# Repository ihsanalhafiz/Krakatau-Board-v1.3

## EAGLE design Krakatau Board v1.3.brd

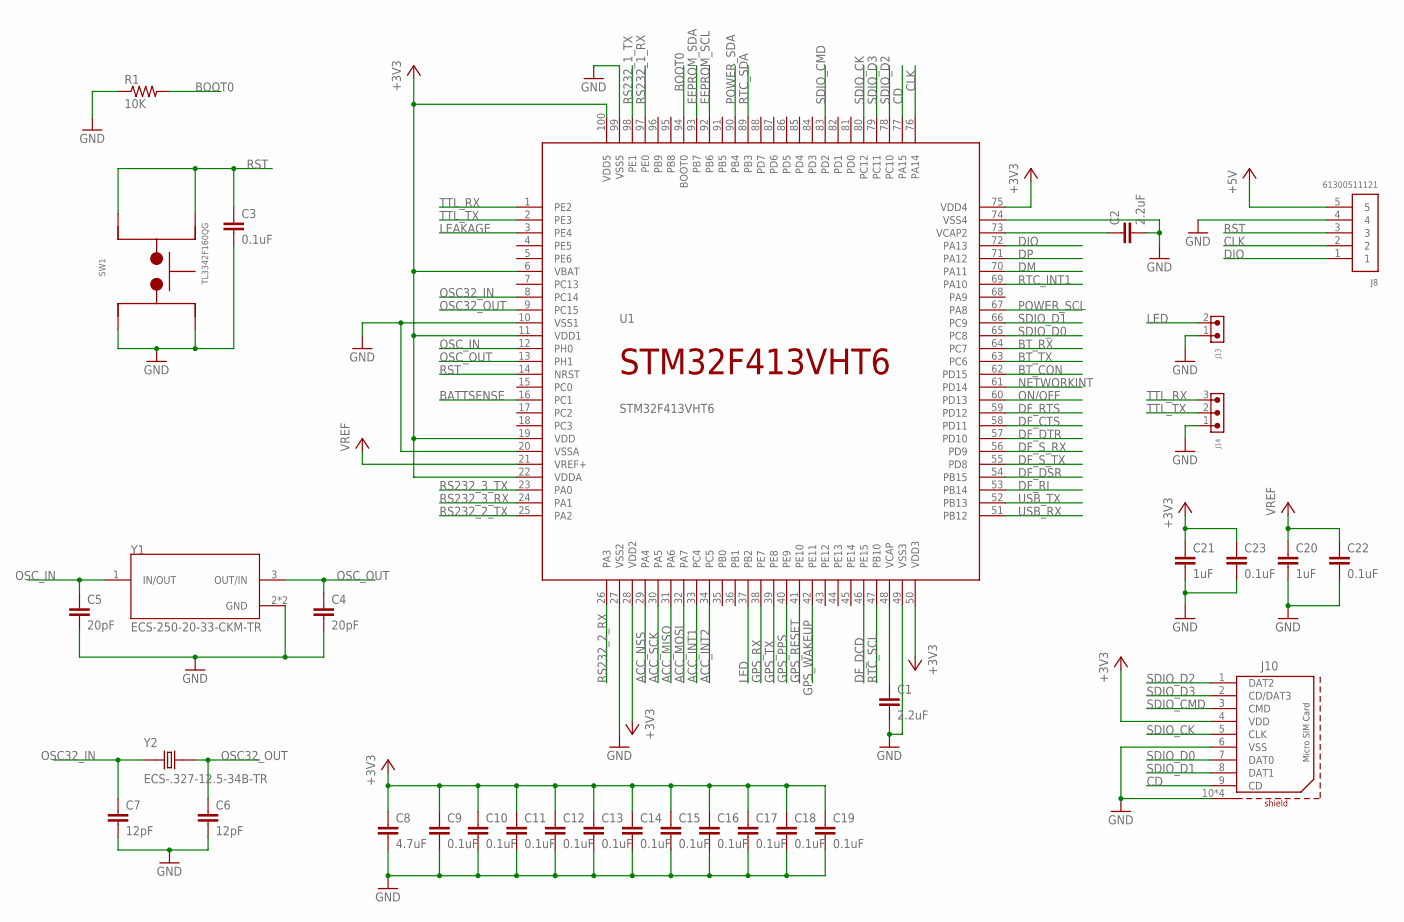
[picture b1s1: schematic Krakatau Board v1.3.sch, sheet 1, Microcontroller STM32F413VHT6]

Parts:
C1, C2: 2.2uF; CAPC1005X50N-0402-KEMET
C3, C9, C10, C11, C12, C13, C14, C15, C16, C17, C18, C19, C22, C23: 0.1uF; CAPC1005X50N-0402-KEMET
C4, C5: 20pF; CAPC1005X50N-0402-KEMET
C6, C7: 12pF; CAPC1005X50N-0402-KEMET
C8: 4.7uF; CAPC3225X90N-1210-KEMET
C20, C21: 1uF; CAPC1608X80N-0603-KEMET
J8: 61300511121
J10: 693071020811
J13: 61900211121
J14: 61900311121
R1: 10K; RESC1005X35N-0402-VISHAYDALE
SW1: TL3342F160QG; SW_TL3342F160QG
U1: STM32F413VHT6; QFP50P1590X1590X160-100N
Y1: ECS-250-20-33-CKM-TR; XTAL_ECS-250-20-33-CKM-TR
Y2: ECS-.327-12.5-34B-TR; XTAL_ECS-.327-12.5-34B-TR

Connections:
+3V3: C8.1, C9.1, C10.1, C11.1, C12.1, C13.1, C14.1, C15.1, C16.1, C17.1, C18.1, C19.1, C21.1, C23.1, J10.4 (VDD), U1.6 (VBAT), U1.11 (VDD1), U1.19 (VDD), U1.22 (VDDA), U1.28 (VDD2), U1.50 (VDD3), U1.75 (VDD4), U1.100 (VDD5); also elsewhere on the board
+5V: J8.5; also elsewhere on the board
ACC_INT1: U1.33 (PC4); also elsewhere on the board
ACC_INT2: U1.34 (PC5); also elsewhere on the board
ACC_MISO: U1.31 (PA6); also elsewhere on the board
ACC_MOSI: U1.32 (PA7); also elsewhere on the board
ACC_NSS: U1.29 (PA4); also elsewhere on the board
ACC_SCK: U1.30 (PA5); also elsewhere on the board
BATTSENSE: U1.16 (PC1); also elsewhere on the board
BOOT0: R1.2, U1.94 (BOOT0)
BT_CON: U1.62 (PD15); also elsewhere on the board
BT_RX: U1.64 (PC7); also elsewhere on the board
BT_TX: U1.63 (PC6); also elsewhere on the board
CD: J10.9 (CD), U1.77 (PA15)
CLK: J8.2, U1.76 (PA14)
DF_CTS: U1.58 (PD11); also elsewhere on the board
DF_DCD: U1.46 (PE15); also elsewhere on the board
DF_DSR: U1.54 (PB15); also elsewhere on the board
DF_DTR: U1.57 (PD10); also elsewhere on the board
DF_RI: U1.53 (PB14); also elsewhere on the board
DF_RTS: U1.59 (PD12); also elsewhere on the board
DF_S_RX: U1.56 (PD9); also elsewhere on the board
DF_S_TX: U1.55 (PD8); also elsewhere on the board
DIO: J8.1, U1.72 (PA13)
DM: U1.70 (PA11)
DP: U1.71 (PA12)
EEPROM_SCL: U1.92 (PB6); also elsewhere on the board
EEPROM_SDA: U1.93 (PB7); also elsewhere on the board
GND: C1.2, C2.2, C3.2, C4.2, C5.2, C6.2, C7.2, C8.2, C9.2, C10.2, C11.2, C12.2, C13.2, C14.2, C15.2, C16.2, C17.2, C18.2, C19.2, C20.2, C21.2, C22.2, C23.2, J8.4, J10.6 (VSS), J10.10 (SHIELD), J10.11 (SHIELD), J10.12 (SHIELD), J10.13 (SHIELD), J13.1, J14.1, R1.1, SW1.1, SW1.2, U1.10 (VSS1), U1.20 (VSSA), U1.27 (VSS2), U1.49 (VSS3), U1.74 (VSS4), U1.99 (VSS5), Y1.2 (GND), Y1.4 (GND); also elsewhere on the board
GPS_PPS: U1.40 (PE9); also elsewhere on the board
GPS_RESET: U1.41 (PE10); also elsewhere on the board
GPS_RX: U1.38 (PE7); also elsewhere on the board
GPS_TX: U1.39 (PE8); also elsewhere on the board
GPS_WAKEUP: U1.42 (PE11); also elsewhere on the board
LEAKAGE: U1.3 (PE4); also elsewhere on the board
LED: J13.2, U1.37 (PB2)
unnamed: C2.1, U1.73 (VCAP2)
unnamed: C1.1, U1.48 (VCAP)
NETWORKINT: U1.61 (PD14); also elsewhere on the board
ON/OFF: U1.60 (PD13); also elsewhere on the board
OSC32_IN: C7.1, U1.8 (PC14), Y2.1
OSC32_OUT: C6.1, U1.9 (PC15), Y2.2
OSC_IN: C5.1, U1.12 (PH0), Y1.1 (IN/OUT)
OSC_OUT: C4.1, U1.13 (PH1), Y1.3 (OUT/IN)
POWER_SCL: U1.67 (PA8); also elsewhere on the board
POWER_SDA: U1.90 (PB4); also elsewhere on the board
RS232_1_RX: U1.97 (PE0); also elsewhere on the board
RS232_1_TX: U1.98 (PE1); also elsewhere on the board
RS232_2_RX: U1.26 (PA3); also elsewhere on the board
RS232_2_TX: U1.25 (PA2); also elsewhere on the board
RS232_3_RX: U1.24 (PA1); also elsewhere on the board
RS232_3_TX: U1.23 (PA0); also elsewhere on the board
RST: C3.1, J8.3, SW1.3, SW1.4, U1.14 (NRST)
RTC_INT1: U1.69 (PA10); also elsewhere on the board
RTC_SCL: U1.47 (PB10); also elsewhere on the board
RTC_SDA: U1.89 (PB3); also elsewhere on the board
SDIO_CK: J10.5 (CLK), U1.80 (PC12)
SDIO_CMD: J10.3 (CMD), U1.83 (PD2)
SDIO_D0: J10.7 (DAT0), U1.65 (PC8)
SDIO_D1: J10.8 (DAT1), U1.66 (PC9)
SDIO_D2: J10.1 (DAT2), U1.78 (PC10)
SDIO_D3: J10.2 (CD/DAT3), U1.79 (PC11)
TTL_RX: J14.3, U1.1 (PE2)
TTL_TX: J14.2, U1.2 (PE3)
USB_RX: U1.51 (PB12); also elsewhere on the board
USB_TX: U1.52 (PB13); also elsewhere on the board
VCC: C20.1, C22.1, U1.21 (VREF+); also elsewhere on the board

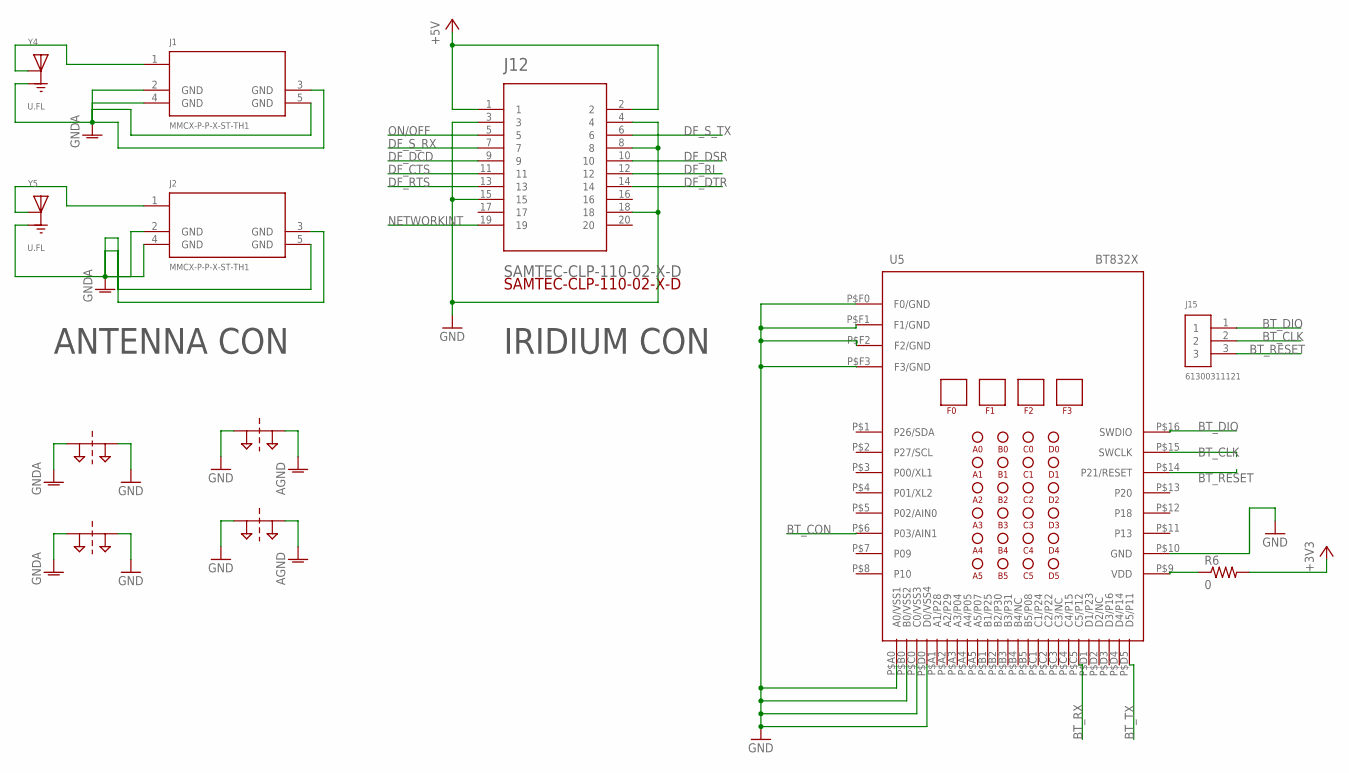
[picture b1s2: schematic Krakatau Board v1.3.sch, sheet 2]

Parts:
J1, J2: MMCX-P-P-X-ST-TH1
J12: SAMTEC-CLP-110-02-X-D
J15: 61300311121
R6: 0; RESC1005X30N
SUPPLY4, SUPPLY5, SUPPLY6, SUPPLY7: 2PT_GND_TIE
U5: BT832X
Y4, Y5: U.FL; HRS_U.FL-R-SMT-1(10)

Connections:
+3V3: R6.2; also elsewhere on the board
+5V: J12.1, J12.2; also elsewhere on the board
AGND: SUPPLY5.P$2, SUPPLY6.P$2; also elsewhere on the board
BT_CLK: J15.2, U5.P$15 (SWCLK)
BT_CON: U5.P$6 (P03/AIN1); also elsewhere on the board
BT_DIO: J15.1, U5.P$16 (SWDIO)
BT_RESET: J15.3, U5.P$14 (P21/RESET)
BT_RX: U5.P$C5 (C5/P12); also elsewhere on the board
BT_TX: U5.P$D5 (D5/P11); also elsewhere on the board
DF_CTS: J12.11; also elsewhere on the board
DF_DCD: J12.9; also elsewhere on the board
DF_DSR: J12.10; also elsewhere on the board
DF_DTR: J12.14; also elsewhere on the board
DF_RI: J12.12; also elsewhere on the board
DF_RTS: J12.13; also elsewhere on the board
DF_S_RX: J12.7; also elsewhere on the board
DF_S_TX: J12.6; also elsewhere on the board
GND: J12.3, J12.4, J12.8, J12.15, J12.18, SUPPLY4.P$2, SUPPLY5.P$1, SUPPLY6.P$1, SUPPLY7.P$2, U5.P$10 (GND), U5.P$A0 (A0/VSS1), U5.P$B0 (B0/VSS2), U5.P$C0 (C0/VSS3), U5.P$D0 (D0/VSS4), U5.P$F0 (F0/GND), U5.P$F1 (F1/GND), U5.P$F2 (F2/GND), U5.P$F3 (F3/GND); also elsewhere on the board
GNDA: J1.2 (GND), J1.3 (GND), J1.4 (GND), J1.5 (GND), J2.2 (GND), J2.3 (GND), J2.4 (GND), J2.5 (GND), SUPPLY4.P$1, SUPPLY7.P$1, Y4.1 (GND), Y4.3 (GND), Y5.1 (GND), Y5.3 (GND)
unnamed: R6.1, U5.P$9 (VDD)
unnamed: J1.1, Y4.2 (SIG)
unnamed: J2.1, Y5.2 (SIG)
NETWORKINT: J12.19; also elsewhere on the board
ON/OFF: J12.5; also elsewhere on the board

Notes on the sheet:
ANTENNA CON
IRIDIUM CON

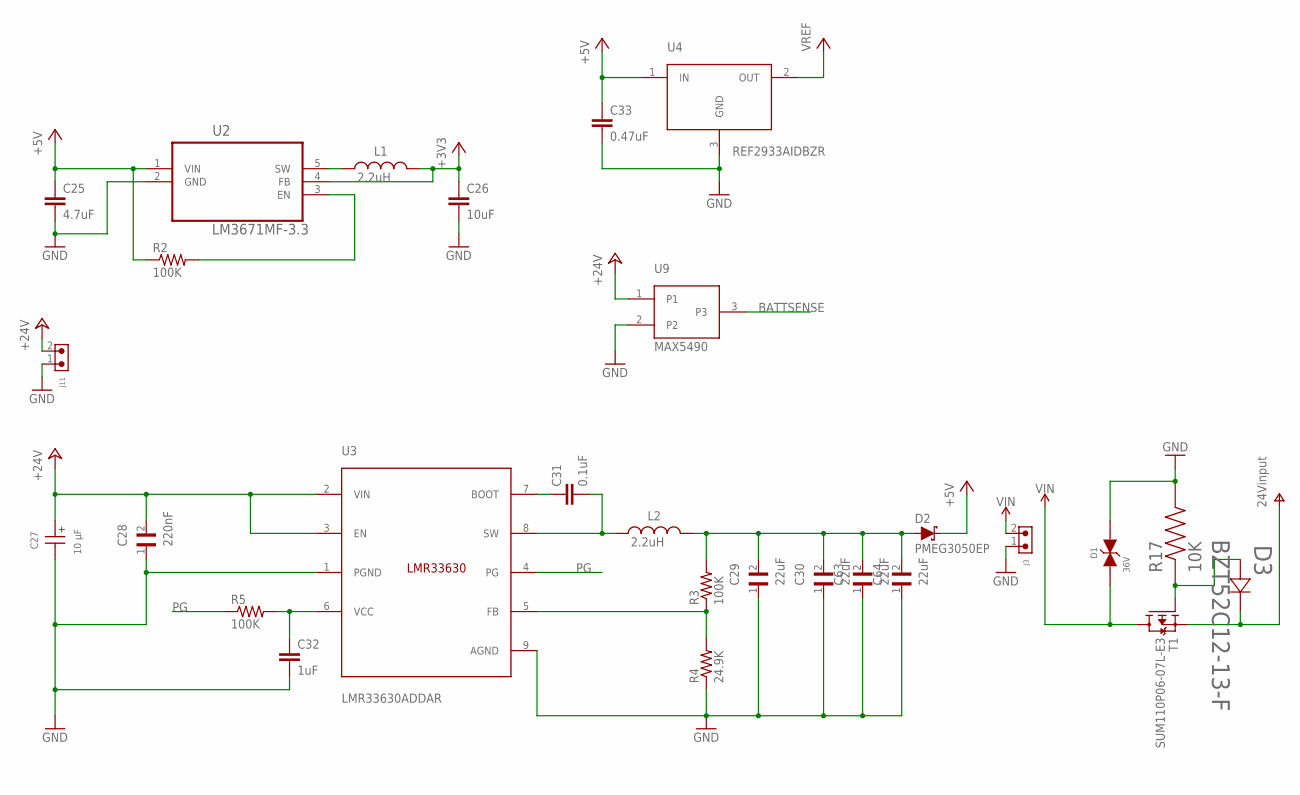
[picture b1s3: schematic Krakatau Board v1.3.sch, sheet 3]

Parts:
C25: 4.7uF; CAPC2113X90N-0805-KEMET
C26: 10uF; CAPC2113X90N-0805-KEMET
C27: 10 µF; WCAP-AS5H_5X5.5(DXL)
C28: 220nF; CAPC2012X100N
C29, C30, C63, C64: 22uF; CAPC2113X95N
C31: 0.1uF; CAPC1005X50N-0402-KEMET
C32: 1uF; CAPC1608X80N-0603-KEMET
C33: 0.47uF; CAPC1005X50N-0402-KEMET
D1: 36V; WE-TVSP_DO-214AB_BIDIRECTIONAL
D2: PMEG3050EP; SODFL4725X110N
D3: BZT52C12-13-F; SOD123_DIO
J3, J11: 61900211021
L1, L2: 2.2uH; WE-MAIA_4020
R2, R3, R5: 100K; RESC1005X35N-0402-VISHAYDALE
R4: 24.9K; RESC1005X30N
R17: 10K; RESC1608X55N
T1: SUM110P06-07L-E3; TO-263AB_SUM
U2: LM3671MF-3.3; SOT95P284X122-5N
U3: LMR33630ADDAR; SOIC127P600X170-9T260X310N
U4: REF2933AIDBZR; SOT95P237X112-3N
U9: MAX5490; SOT95P237X110-3

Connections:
+3V3: C26.1, L1.2, U2.4 (FB); also elsewhere on the board
+5V: C25.1, C33.1, D2.C, R2.1, U2.1 (VIN), U4.1 (IN); also elsewhere on the board
+24V: C27.1 (+), C28.2, J11.2, U3.2 (VIN), U3.3 (EN), U9.1; also elsewhere on the board
BATTSENSE: U9.3; also elsewhere on the board
GND: C25.2, C26.2, C27.2 (-), C28.1, C29.1, C30.1, C32.2, C33.2, C63.1, C64.1, D1.2, J3.1, J11.1, R4.1, R17.2, U2.2 (GND), U3.1 (PGND), U3.9 (AGND), U4.3 (GND), U9.2; also elsewhere on the board
unnamed: L1.1, U2.5 (SW)
unnamed: C31.1, U3.7 (BOOT)
unnamed: C29.2, C30.2, C63.2, C64.2, D2.A, L2.2, R3.2
unnamed: C32.1, R5.2, U3.6 (VCC)
unnamed: C31.2, L2.1, U3.8 (SW)
unnamed: R3.1, R4.2, U3.5 (FB)
unnamed: D3.2, R17.1, T1.1 (G)
unnamed: R2.2, U2.3 (EN)
PG: R5.1, U3.4 (PG)
V+: D3.1, T1.3 (S); also elsewhere on the board
VCC: U4.2 (OUT); also elsewhere on the board
VIN: D1.1, J3.2, T1.2 (D)

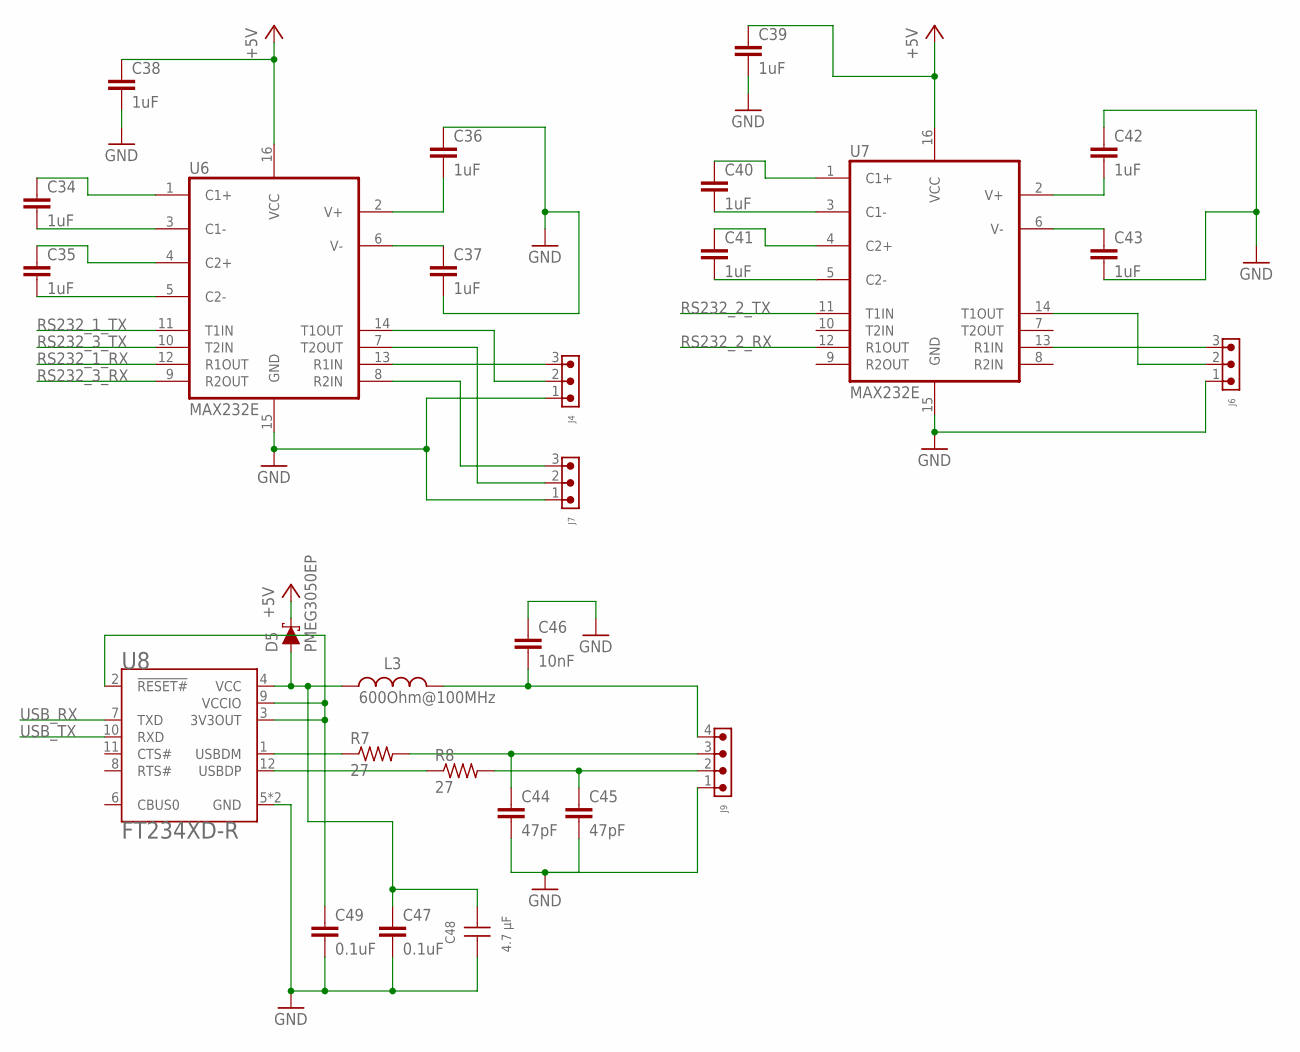
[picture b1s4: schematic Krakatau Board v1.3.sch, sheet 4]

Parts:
C34, C35, C36, C37, C38, C39, C40, C41, C42, C43: 1uF; CAPC1608X80N-0603-KEMET
C44, C45: 47pF; CAPC1005X50N-0402-KEMET
C46: 10nF; CAPC1005X50N-0402-KEMET
C47, C49: 0.1uF; CAPC1005X50N-0402-KEMET
C48: 4.7 µF; WCAP-CSGP_0402
D5: PMEG3050EP; SODFL4725X110N
J4, J6, J7: 61900311021
J9: 61900411121
L3: 600Ohm@100MHz; WE-CBF_0603(W=2.6)
R7, R8: 27; RESC1005X30N
U6, U7: MAX232E; SOIC127P1030X265-16N
U8: FT234XD-R; SON45P300X300X75-13N

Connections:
+5V: C38.1, C39.1, D5.C, U6.16 (VCC), U7.16 (VCC); also elsewhere on the board
GND: C36.1, C37.2, C38.2, C39.2, C42.1, C43.2, C44.2, C45.2, C46.1, C47.2, C48.1, C49.2, J4.1, J6.1, J7.1, J9.1, U6.15 (GND), U7.15 (GND), U8.5 (GND), U8.13 (GND); also elsewhere on the board
unnamed: J6.2, U7.14 (T1OUT)
unnamed: J6.3, U7.13 (R1IN)
unnamed: C34.1, U6.1 (C1+)
unnamed: C34.2, U6.3 (C1-)
unnamed: C35.1, U6.4 (C2+)
unnamed: J4.2, U6.14 (T1OUT)
unnamed: J4.3, U6.13 (R1IN)
unnamed: J7.2, U6.7 (T2OUT)
unnamed: J7.3, U6.8 (R2IN)
unnamed: C35.2, U6.5 (C2-)
unnamed: C36.2, U6.2 (V+)
unnamed: C37.1, U6.6 (V-)
unnamed: C40.2, U7.3 (C1-)
unnamed: C40.1, U7.1 (C1+)
unnamed: C41.1, U7.4 (C2+)
unnamed: C41.2, U7.5 (C2-)
unnamed: C43.1, U7.6 (V-)
unnamed: C42.2, U7.2 (V+)
unnamed: R7.1, U8.1 (USBDM)
unnamed: R8.1, U8.12 (USBDP)
unnamed: C44.1, J9.3, R7.2
unnamed: C45.1, J9.2, R8.2
unnamed: C46.2, J9.4, L3.2
unnamed: C49.1, U8.2 (!RESET#), U8.3 (3V3OUT), U8.9 (VCCIO)
unnamed: C47.1, C48.2, D5.A, L3.1, U8.4 (VCC)
RS232_1_RX: U6.12 (R1OUT); also elsewhere on the board
RS232_1_TX: U6.11 (T1IN); also elsewhere on the board
RS232_2_RX: U7.12 (R1OUT); also elsewhere on the board
RS232_2_TX: U7.11 (T1IN); also elsewhere on the board
RS232_3_RX: U6.9 (R2OUT); also elsewhere on the board
RS232_3_TX: U6.10 (T2IN); also elsewhere on the board
USB_RX: U8.7 (TXD); also elsewhere on the board
USB_TX: U8.10 (RXD); also elsewhere on the board

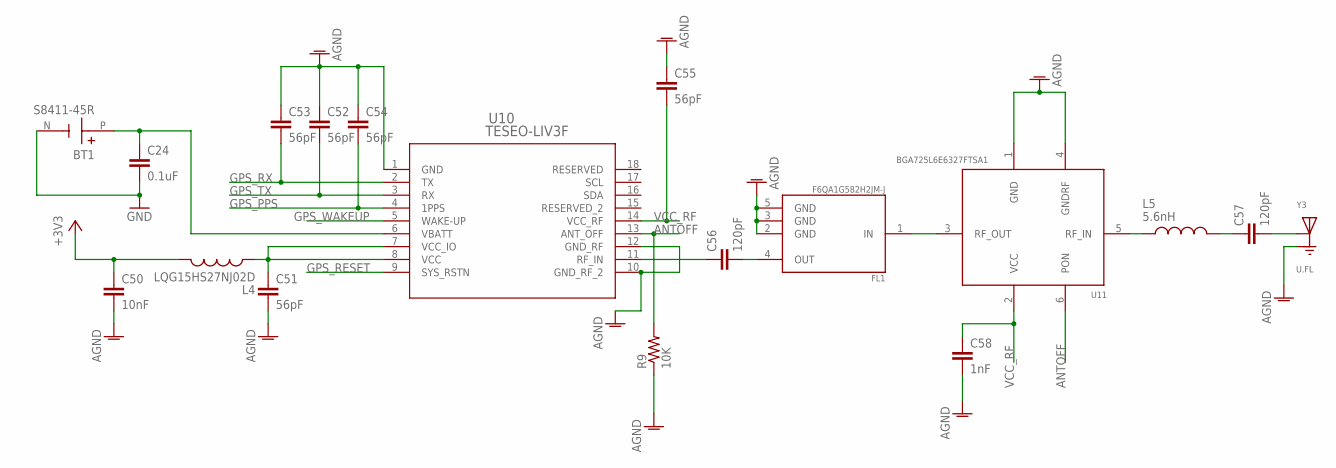
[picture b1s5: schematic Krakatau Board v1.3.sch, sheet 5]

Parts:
BT1: S8411-45R; BAT_S8411-45R
C24: 0.1uF; CAPC1005X50N-0402-KEMET
C50: 10nF; CAPC1005X50N-0402-KEMET
C51, C52, C53, C54, C55: 56pF; CAPC1005X50N-0402-KEMET
C56, C57: 120pF; CAPC1005X50N-0402-KEMET
C58: 1nF; CAPC1005X50N-0402-KEMET
FL1: F6QA1G582H2JM-J; FIL_F6QA1G582H2JM-J
L4: LQG15HS27NJ02D; INDC1005X55N
L5: 5.6nH; INDC1006X60N
R9: 10K; RESC1005X35N-0402-VISHAYDALE
U10: TESEO-LIV3F; LCC18_9P7X10P1
U11: BGA725L6E6327FTSA1; INF-TSLP-6-2_V_1PRIMARY
Y3: U.FL; HRS_U.FL-R-SMT-1(10)

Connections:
+3V3: C50.1, L4.2; also elsewhere on the board
AGND: C50.2, C51.2, C52.1, C53.1, C54.1, C55.1, C58.2, FL1.2 (GND), FL1.3 (GND), FL1.5 (GND), R9.1, U10.1 (GND), U10.10 (GND_RF_2), U10.12 (GND_RF), U11.1 (GND), U11.4 (GNDRF), Y3.1 (GND), Y3.3 (GND); also elsewhere on the board
ANTOFF: R9.2, U10.13 (ANT_OFF), U11.6 (PON)
GND: BT1.N (-), C24.2; also elsewhere on the board
GPS_PPS: C54.2, U10.4 (1PPS); also elsewhere on the board
GPS_RESET: U10.9 (SYS_RSTN); also elsewhere on the board
GPS_RX: C53.2, U10.2 (TX); also elsewhere on the board
GPS_TX: C52.2, U10.3 (RX); also elsewhere on the board
GPS_WAKEUP: U10.5 (WAKE-UP); also elsewhere on the board
unnamed: C51.1, L4.1, U10.7 (VCC_IO), U10.8 (VCC)
unnamed: C56.2, FL1.4 (OUT)
unnamed: C56.1, U10.11 (RF_IN)
unnamed: FL1.1 (IN), U11.3 (RF_OUT)
unnamed: L5.1, U11.5 (RF_IN)
unnamed: C57.1, L5.2
unnamed: C57.2, Y3.2 (SIG)
VBAT: BT1.P (+), C24.1, U10.6 (VBATT)
VCC_RF: C55.2, C58.1, U10.14 (VCC_RF), U11.2 (VCC)

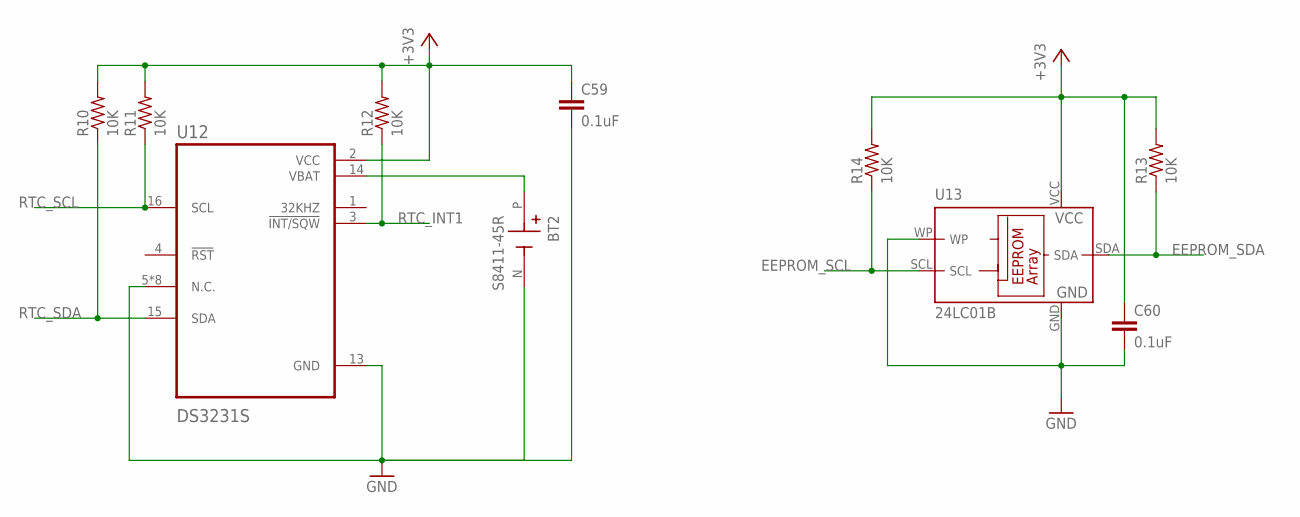
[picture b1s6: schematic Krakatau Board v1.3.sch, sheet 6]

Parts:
BT2: S8411-45R; BAT_S8411-45R
C59, C60: 0.1uF; CAPC1005X50N-0402-KEMET
R10, R11, R12, R13, R14: 10K; RESC1005X35N-0402-VISHAYDALE
U12: DS3231S; SOIC127P1032X265-16N
U13: 24LC01B; SOT23-5L

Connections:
+3V3: C59.1, C60.1, R10.2, R11.2, R12.2, R13.2, R14.2, U12.2 (VCC), U13.VCC; also elsewhere on the board
EEPROM_SCL: R14.1, U13.SCL; also elsewhere on the board
EEPROM_SDA: R13.1, U13.SDA; also elsewhere on the board
GND: BT2.N (-), C59.2, C60.2, U12.5 (N.C.), U12.6 (N.C.), U12.7 (N.C.), U12.8 (N.C.), U12.9 (N.C.), U12.10 (N.C.), U12.11 (N.C.), U12.12 (N.C.), U12.13 (GND), U13.GND, U13.WP; also elsewhere on the board
unnamed: BT2.P (+), U12.14 (VBAT)
RTC_INT1: R12.1, U12.3 (!INT/SQW); also elsewhere on the board
RTC_SCL: R11.1, U12.16 (SCL); also elsewhere on the board
RTC_SDA: R10.1, U12.15 (SDA); also elsewhere on the board

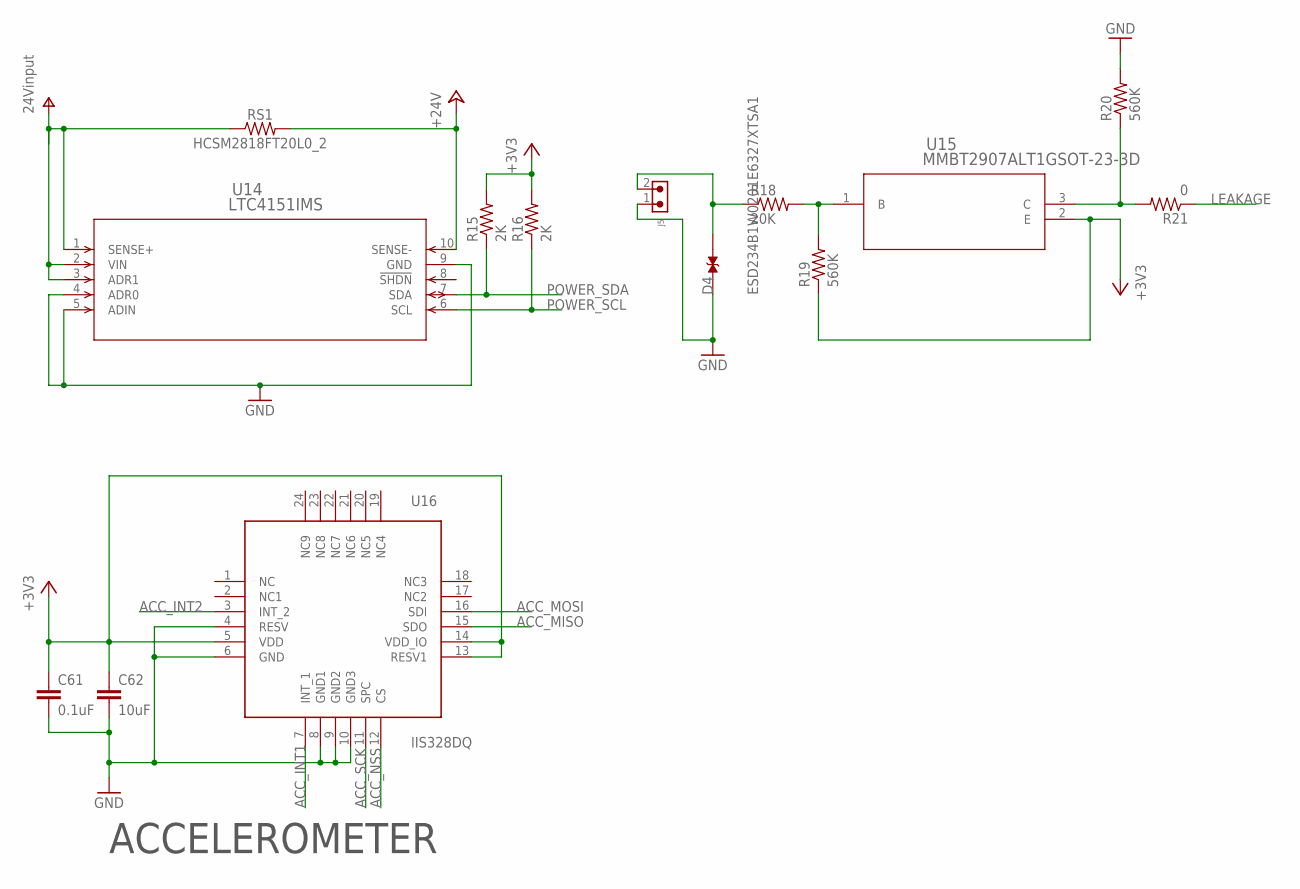
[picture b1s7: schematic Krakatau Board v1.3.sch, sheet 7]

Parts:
C61: 0.1uF; CAPC1005X50N-0402-KEMET
C62: 10uF; CAPC1005X50N-0402-KEMET
D4: ESD234B1W0201E6327XTSA1; DIODFN58X28X16-2N
J5: 61900211021
R15, R16: 2K; RESC1005X35N-0402-VISHAYDALE
R18: 20K; RESC1005X35N-0402-VISHAYDALE
R19, R20: 560K; RESC1005X35N-0402-VISHAYDALE
R21: 0; RESC1005X35N-0402-VISHAYDALE
RS1: HCSM2818FT20L0_2; RESM7149X165NR
U14: LTC4151IMS; SOP50P490X110-10N
U15: MMBT2907ALT1GSOT-23-3D; SOT95P237X110-3
U16: IIS328DQ; QFN50P400X400X100-24

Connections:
+3V3: C61.1, C62.1, R15.2, R16.2, R19.1, U15.2 (E), U16.5 (VDD), U16.13 (RESV1), U16.14 (VDD_IO); also elsewhere on the board
+24V: RS1.2, U14.10 (SENSE-); also elsewhere on the board
ACC_INT1: U16.7 (INT_1); also elsewhere on the board
ACC_INT2: U16.3 (INT_2); also elsewhere on the board
ACC_MISO: U16.15 (SDO); also elsewhere on the board
ACC_MOSI: U16.16 (SDI); also elsewhere on the board
ACC_NSS: U16.12 (CS); also elsewhere on the board
ACC_SCK: U16.11 (SPC); also elsewhere on the board
GND: C61.2, C62.2, D4.1, J5.1, R20.2, U14.4 (ADR0), U14.5 (ADIN), U14.9 (GND), U16.4 (RESV), U16.6 (GND), U16.8 (GND1), U16.9 (GND2), U16.10 (GND3); also elsewhere on the board
LEAKAGE: R21.1; also elsewhere on the board
unnamed: D4.2, J5.2, R18.1
unnamed: R18.2, R19.2, U15.1 (B)
unnamed: R20.1, R21.2, U15.3 (C)
POWER_SCL: R16.1, U14.6 (SCL); also elsewhere on the board
POWER_SDA: R15.1, U14.7 (SDA); also elsewhere on the board
V+: RS1.1, U14.1 (SENSE+), U14.2 (VIN), U14.3 (ADR1); also elsewhere on the board

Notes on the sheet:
ACCELEROMETER

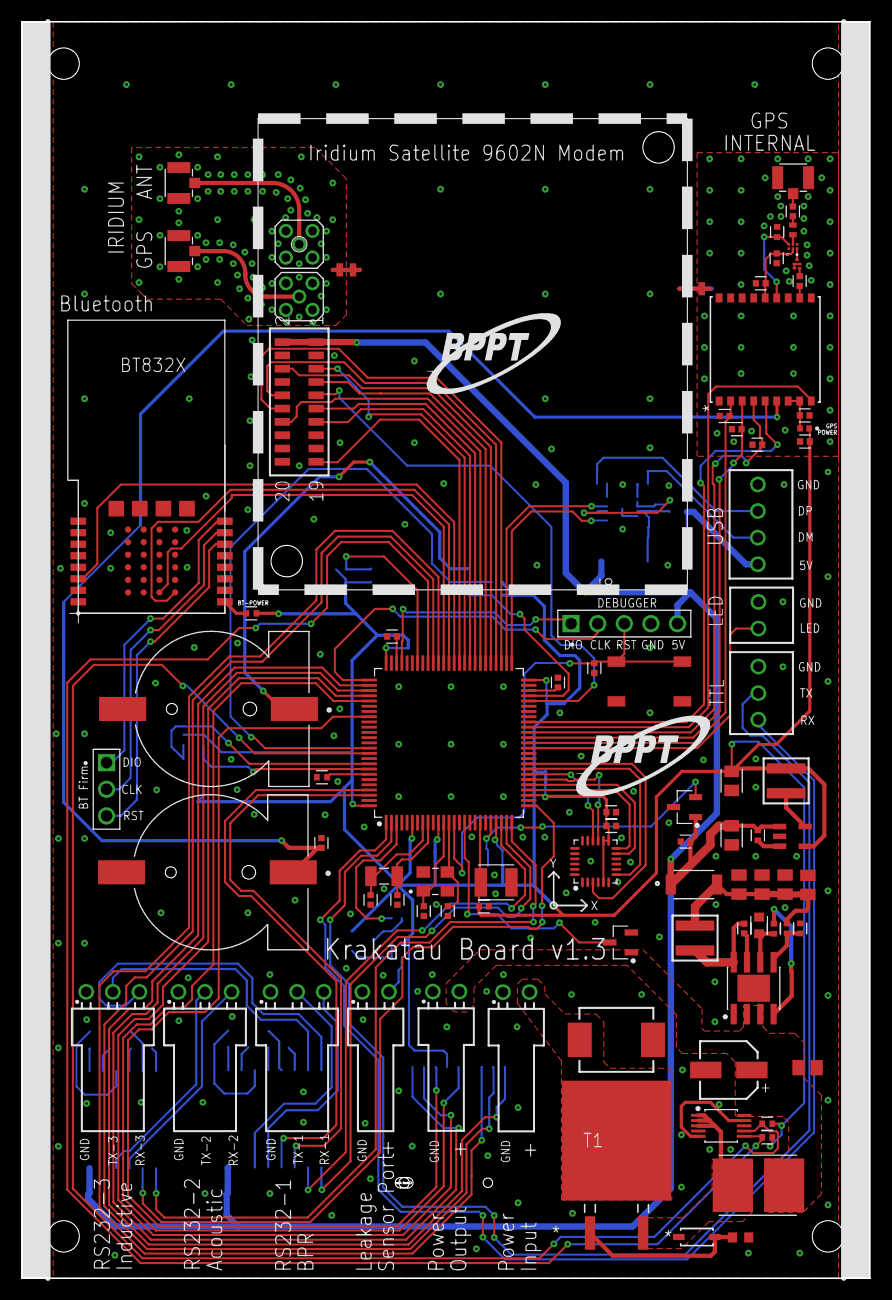
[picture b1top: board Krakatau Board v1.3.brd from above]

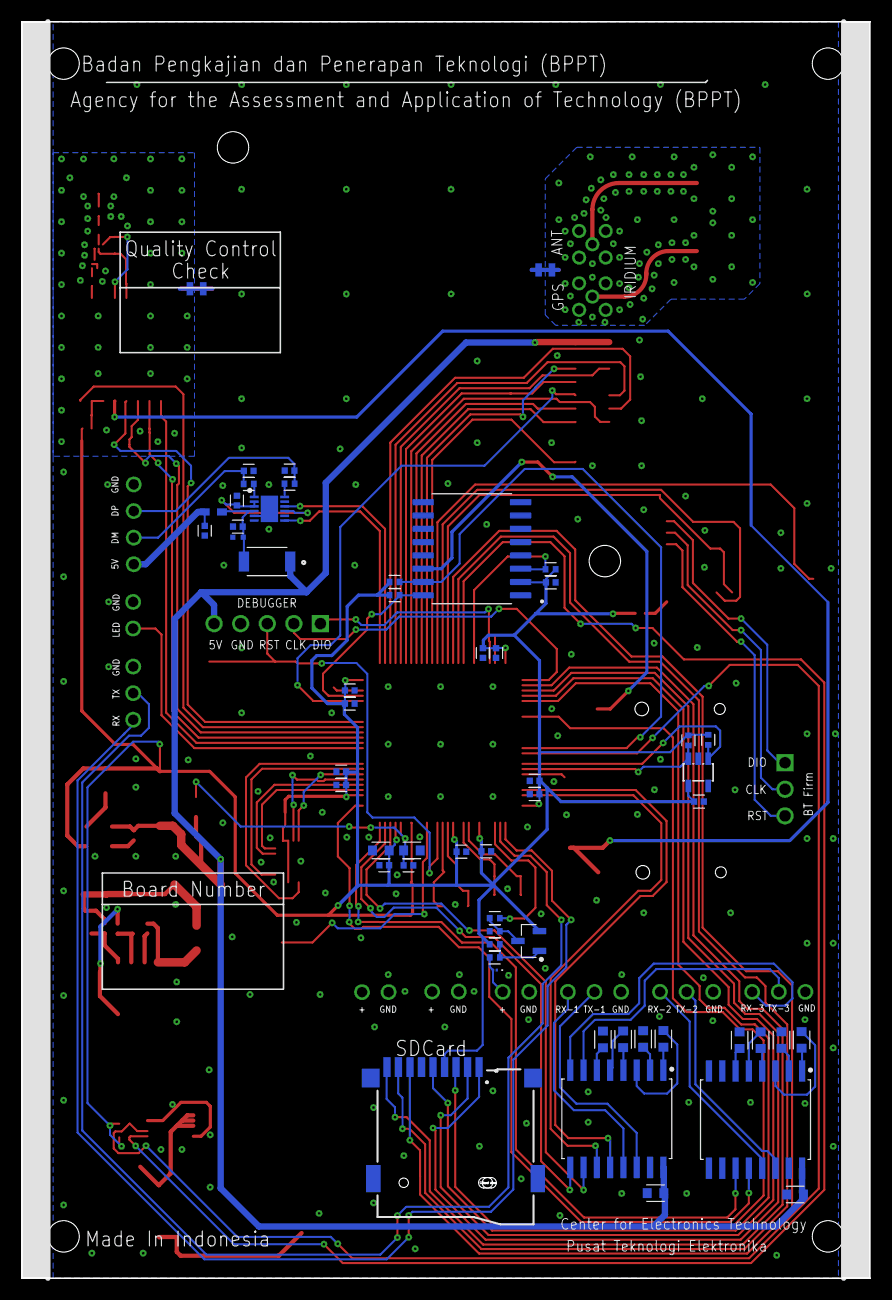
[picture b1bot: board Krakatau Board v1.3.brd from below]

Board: 2 copper layers, 81.0 x 120.0 mm, 141 parts (55 on the bottom side), 124 nets.

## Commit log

2020-05-08 finalisasi
2020-05-08 update BoM fix cek 08 mei 2020
2020-05-09 vias 0.25 min pcbway for 2mm

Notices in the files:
parts and their libraries:
Wurth_Automotive_WE-MAIA: Copyright: Würth Elektronik
SparkFun-PowerSymbols: Licensing: Creative Commons ShareAlike 4.0 International - https://creativecommons.org/licenses/by-sa/4.0
COPYRIGHT: Copyright (C) 2018 Accelerated Designs. All rights reserved
